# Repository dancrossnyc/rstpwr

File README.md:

# rstpwr

This is, fundamentally, a set of serial-controlled solid-state
switches.  I used them to control the power and reset functions
of development machines with ATX motherboards.

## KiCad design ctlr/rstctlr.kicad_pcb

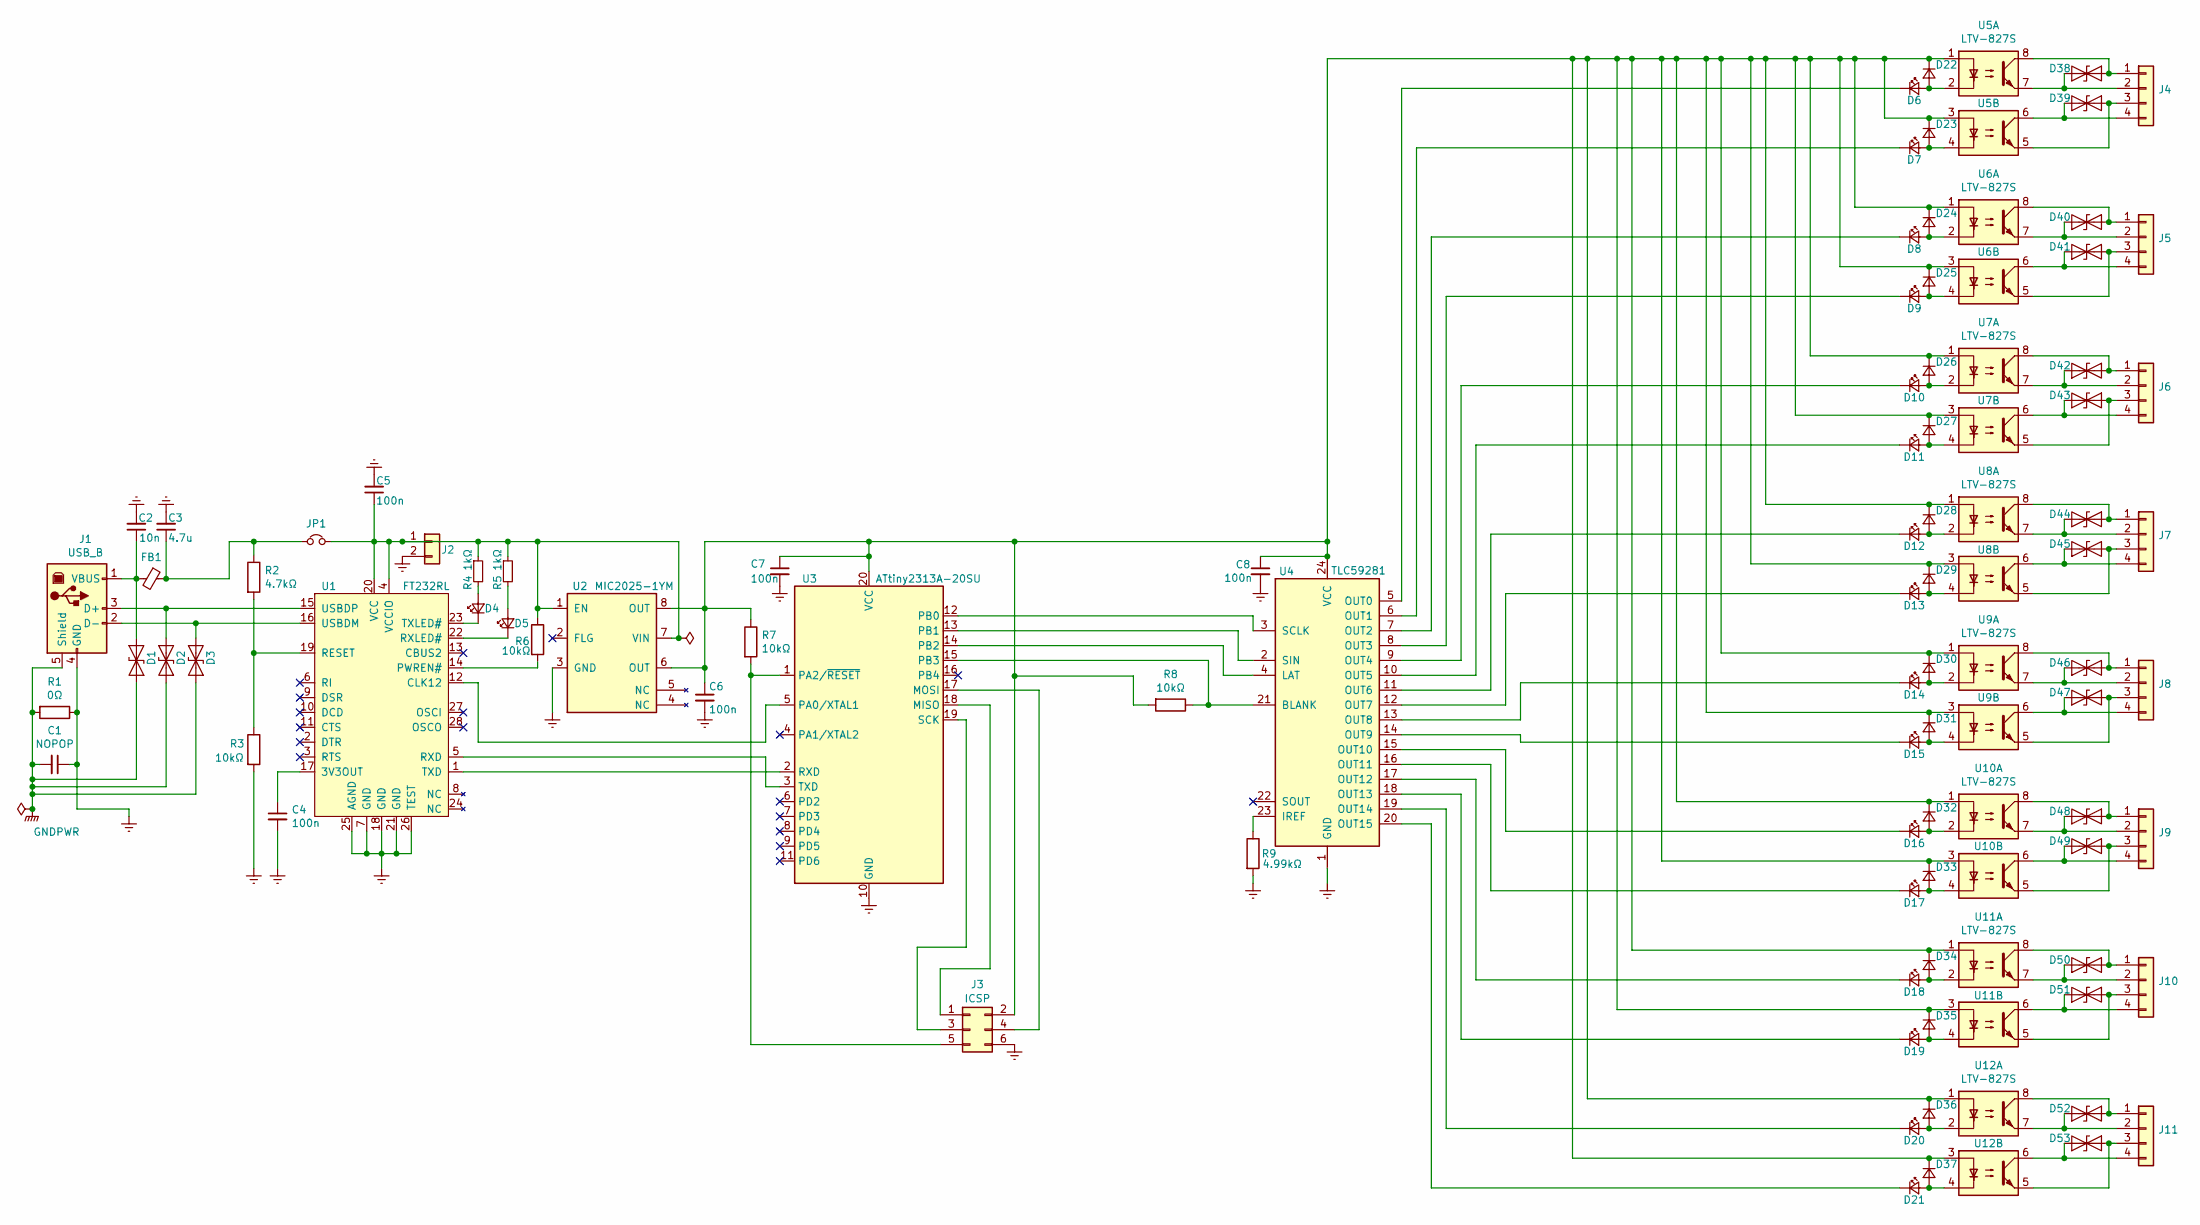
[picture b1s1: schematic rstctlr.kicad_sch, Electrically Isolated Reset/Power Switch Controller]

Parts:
C1: NOPOP; C_0805_2012Metric
C2: 10n; C_0805_2012Metric
C3: 4.7u; C_0805_2012Metric
C4, C5, C6, C7, C8: 100n; C_0805_2012Metric
D1, D2, D3, D22, D23, D24, D25, D26, D27, D28, D29, D30, D31, D32, D33, D34, D35, D36, D37: D_0805_2012Metric
D4, D6, D8, D10, D12, D14, D16, D18, D20: RED; LED_0805_2012Metric
D5, D7, D9, D11, D13, D15, D17, D19, D21: GRN; LED_0805_2012Metric
D38, D39, D40, D41, D42, D43, D44, D45, D46, D47, D48, D49, D50, D51, D52, D53: D_SOD-323_HandSoldering
FB1: FB; L_0805_2012Metric
J1: USB_B; USB_B_OST_USB-B1HSxx_Horizontal
J2: PinHeader_1x02_P2.54mm_Vertical
J3: ICSP; PinHeader_2x03_P2.54mm_Vertical
J4, J5, J6, J7, J8, J9, J10, J11: Molex_SPOX_5267-04A_1x04_P2.50mm_Vertical
JP1: PinHeader_1x02_P2.54mm_Vertical
R1: 0Ω; R_0805_2012Metric
R2: 4.7kΩ; R_0805_2012Metric
R3, R6, R7, R8: 10kΩ; R_0805_2012Metric
R4, R5: 1kΩ; R_0805_2012Metric
R9: 4.99kΩ; R_0805_2012Metric
U1: FT232RL; SSOP-28_5.3x10.2mm_P0.65mm
U2: MIC2025-1YM; SOIC-8_3.9x4.9mm_P1.27mm
U3: ATtiny2313A-20SU; SOIC-20W_7.5x12.8mm_P1.27mm
U4: TLC59281; SSOP-24_3.9x8.7mm_P0.635mm
U5, U6, U7, U8, U9, U10, U11, U12: LTV-827S; SMDIP-8_W9.53mm

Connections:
Earth: C1.1, C2.2, C3.2, C4.2, C5.2, C6.2, C7.2, C8.2, J1.4 (GND), J2.2, J3.6, R1.1, R3.2, R9.2, U1.7 (GND), U1.18 (GND), U1.21 (GND), U1.25 (AGND), U1.26 (TEST), U2.3 (GND), U3.10 (GND), U4.1 (GND)
GNDPWR: C1.2, D1.2 (A2), D2.2 (A2), D3.2 (A2), J1.5 (Shield), R1.2
unnamed: C2.1, D1.1 (A1), FB1.2, J1.1 (VBUS)
unnamed: C3.1, FB1.1, JP1.1, R2.1
unnamed: C4.1, U1.17 (3V3OUT)
unnamed: C5.1, J2.1, JP1.2, R4.1, R5.1, R6.1, U1.4 (VCCIO), U1.20 (VCC), U2.1 (EN), U2.7 (VIN)
unnamed: C6.1, C7.1, C8.1, D22.1 (K), D23.1 (K), D24.1 (K), D25.1 (K), D26.1 (K), D27.1 (K), D28.1 (K), D29.1 (K), D30.1 (K), D31.1 (K), D32.1 (K), D33.1 (K), D34.1 (K), D35.1 (K), D36.1 (K), D37.1 (K), J3.2, R7.1, R8.2, U2.6 (OUT), U2.8 (OUT), U3.20 (VCC), U4.24 (VCC), U5.1, U5.3, U6.1, U6.3, U7.1, U7.3, U8.1, U8.3, U9.1, U9.3, U10.1, U10.3, U11.1, U11.3, U12.1, U12.3
unnamed: D2.1 (A1), J1.3 (D+), U1.15 (USBDP)
unnamed: D3.1 (A1), J1.2 (D-), U1.16 (USBDM)
unnamed: D4.1 (K), U1.23 (TXLED#)
unnamed: D4.2 (A), R4.2
unnamed: D5.1 (K), U1.22 (RXLED#)
unnamed: D5.2 (A), R5.2
unnamed: D6.1 (K), U4.5 (OUT0)
unnamed: D7.1 (K), U4.6 (OUT1)
unnamed: D8.1 (K), U4.7 (OUT2)
unnamed: D9.1 (K), U4.8 (OUT3)
unnamed: D10.1 (K), U4.9 (OUT4)
unnamed: D10.2 (A), D26.2 (A), U7.2
unnamed: D11.1 (K), U4.10 (OUT5)
unnamed: D11.2 (A), D27.2 (A), U7.4
unnamed: D12.1 (K), U4.11 (OUT6)
unnamed: D12.2 (A), D28.2 (A), U8.2
unnamed: D13.1 (K), U4.12 (OUT7)
unnamed: D13.2 (A), D29.2 (A), U8.4
unnamed: D14.1 (K), U4.13 (OUT8)
unnamed: D14.2 (A), D30.2 (A), U9.2
unnamed: D15.1 (K), U4.14 (OUT9)
unnamed: D15.2 (A), D31.2 (A), U9.4
unnamed: D16.1 (K), U4.15 (OUT10)
unnamed: D16.2 (A), D32.2 (A), U10.2
unnamed: D17.1 (K), U4.16 (OUT11)
unnamed: D17.2 (A), D33.2 (A), U10.4
unnamed: D18.1 (K), U4.17 (OUT12)
unnamed: D18.2 (A), D34.2 (A), U11.2
unnamed: D19.1 (K), U4.18 (OUT13)
unnamed: D19.2 (A), D35.2 (A), U11.4
unnamed: D20.1 (K), U4.19 (OUT14)
unnamed: D20.2 (A), D36.2 (A), U12.2
unnamed: D21.1 (K), U4.20 (OUT15)
unnamed: D21.2 (A), D37.2 (A), U12.4
unnamed: D6.2 (A), D22.2 (A), U5.2
unnamed: D7.2 (A), D23.2 (A), U5.4
unnamed: D8.2 (A), D24.2 (A), U6.2
unnamed: D9.2 (A), D25.2 (A), U6.4
unnamed: D38.1 (A1), J4.1, U5.8
unnamed: D38.2 (A2), J4.2, U5.7
unnamed: D39.1 (A1), J4.3, U5.5
unnamed: D39.2 (A2), J4.4, U5.6
unnamed: D40.1 (A1), J5.1, U6.8
unnamed: D40.2 (A2), J5.2, U6.7
unnamed: D41.1 (A1), J5.3, U6.5
unnamed: D41.2 (A2), J5.4, U6.6
unnamed: D42.1 (A1), J6.1, U7.8
unnamed: D42.2 (A2), J6.2, U7.7
unnamed: D43.1 (A1), J6.3, U7.5
unnamed: D43.2 (A2), J6.4, U7.6
unnamed: D44.1 (A1), J7.1, U8.8
unnamed: D44.2 (A2), J7.2, U8.7
unnamed: D45.1 (A1), J7.3, U8.5
unnamed: D45.2 (A2), J7.4, U8.6
unnamed: D46.1 (A1), J8.1, U9.8
unnamed: D46.2 (A2), J8.2, U9.7
unnamed: D47.1 (A1), J8.3, U9.5
unnamed: D47.2 (A2), J8.4, U9.6
unnamed: D48.1 (A1), J9.1, U10.8
unnamed: D48.2 (A2), J9.2, U10.7
unnamed: D49.1 (A1), J9.3, U10.5
unnamed: D49.2 (A2), J9.4, U10.6
unnamed: D50.1 (A1), J10.1, U11.8
unnamed: D50.2 (A2), J10.2, U11.7
unnamed: D51.1 (A1), J10.3, U11.5
unnamed: D51.2 (A2), J10.4, U11.6
unnamed: D52.1 (A1), J11.1, U12.8
unnamed: D52.2 (A2), J11.2, U12.7
unnamed: D53.1 (A1), J11.3, U12.5
unnamed: D53.2 (A2), J11.4, U12.6
unnamed: J3.1, U3.18 (MISO)
unnamed: J3.3, U3.19 (SCK)
unnamed: J3.4, U3.17 (MOSI)
unnamed: J3.5, R7.2, U3.1 (PA2/~RESET)
unnamed: R2.2, R3.1, U1.19 (RESET)
unnamed: R6.2, U1.14 (PWREN#)
unnamed: R8.1, U3.15 (PB3), U4.21 (BLANK)
unnamed: R9.1, U4.23 (IREF)
unnamed: U1.1 (TXD), U3.2 (RXD)
unnamed: U1.5 (RXD), U3.3 (TXD)
unnamed: U1.12 (CLK12), U3.5 (PA0/XTAL1)
unnamed: U3.12 (PB0), U4.3 (SCLK)
unnamed: U3.13 (PB1), U4.2 (SIN)
unnamed: U3.14 (PB2), U4.4 (LAT)

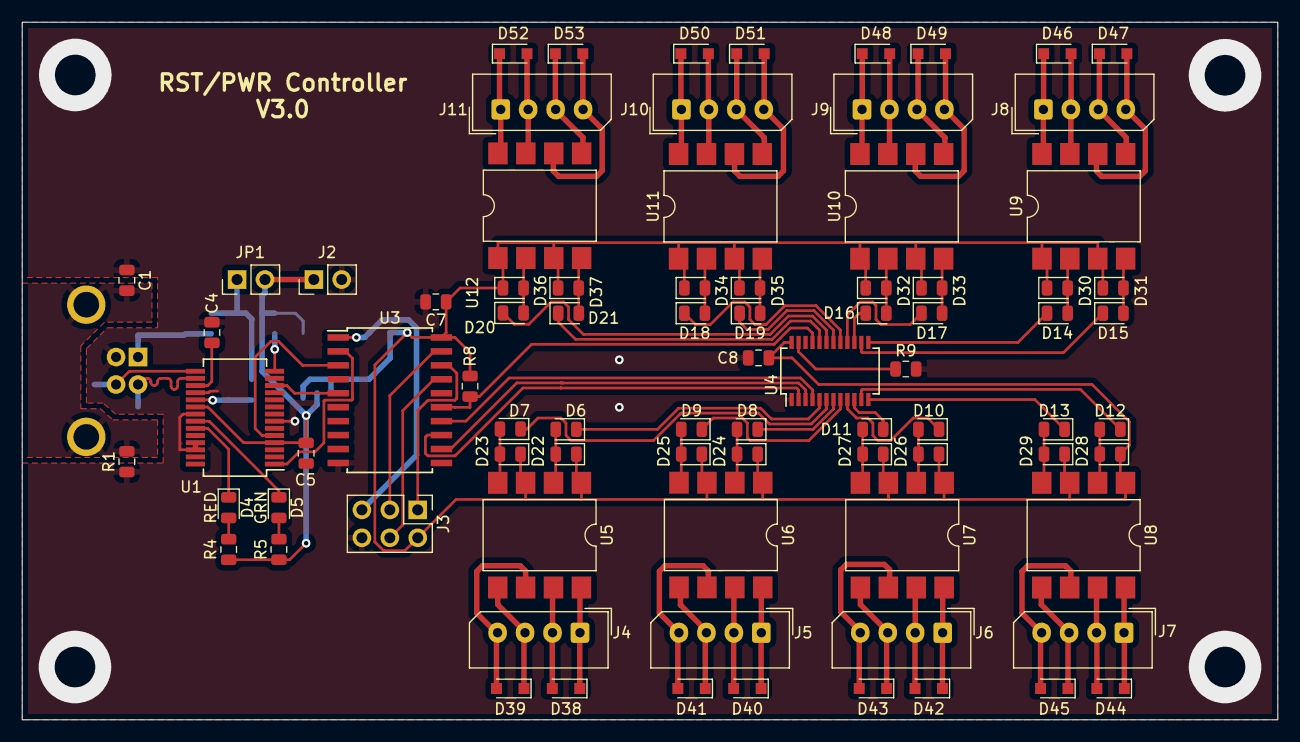
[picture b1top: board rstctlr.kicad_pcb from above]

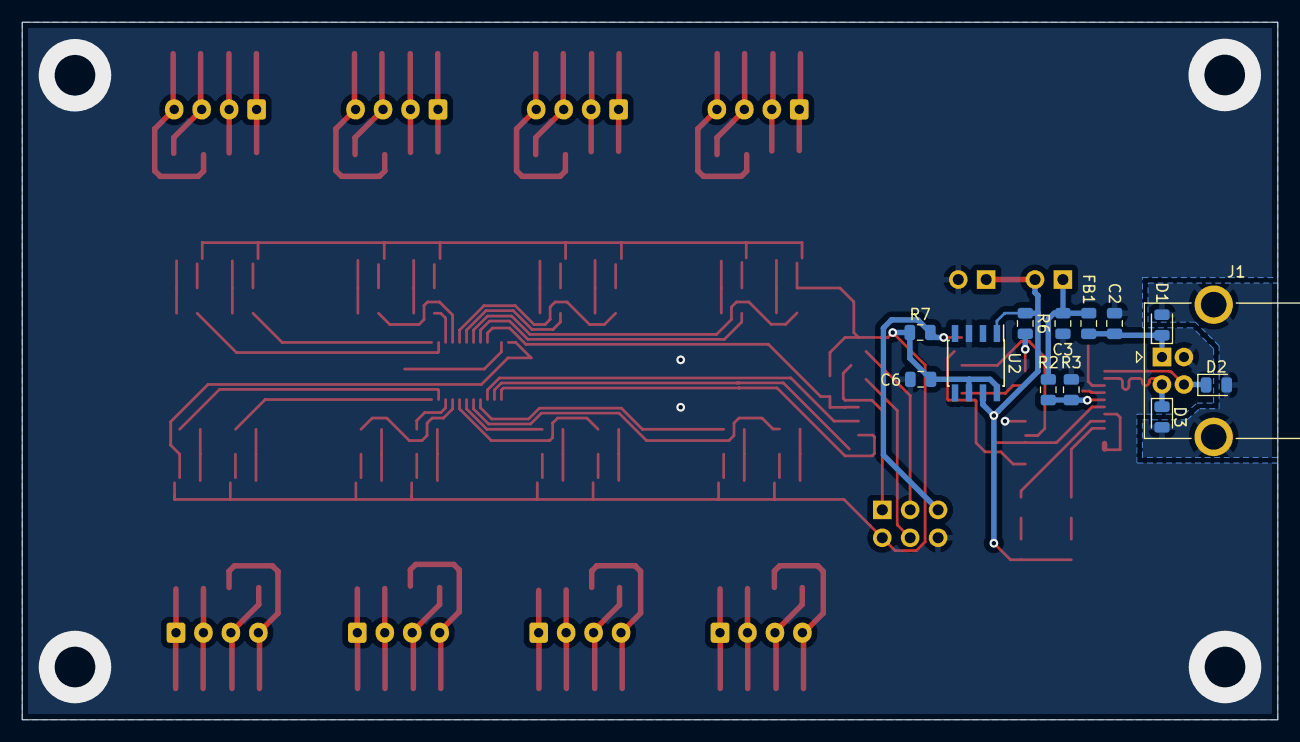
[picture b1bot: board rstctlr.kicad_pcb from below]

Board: 2 copper layers, 114.3 x 63.5 mm, 95 parts (13 on the bottom side), 91 nets.

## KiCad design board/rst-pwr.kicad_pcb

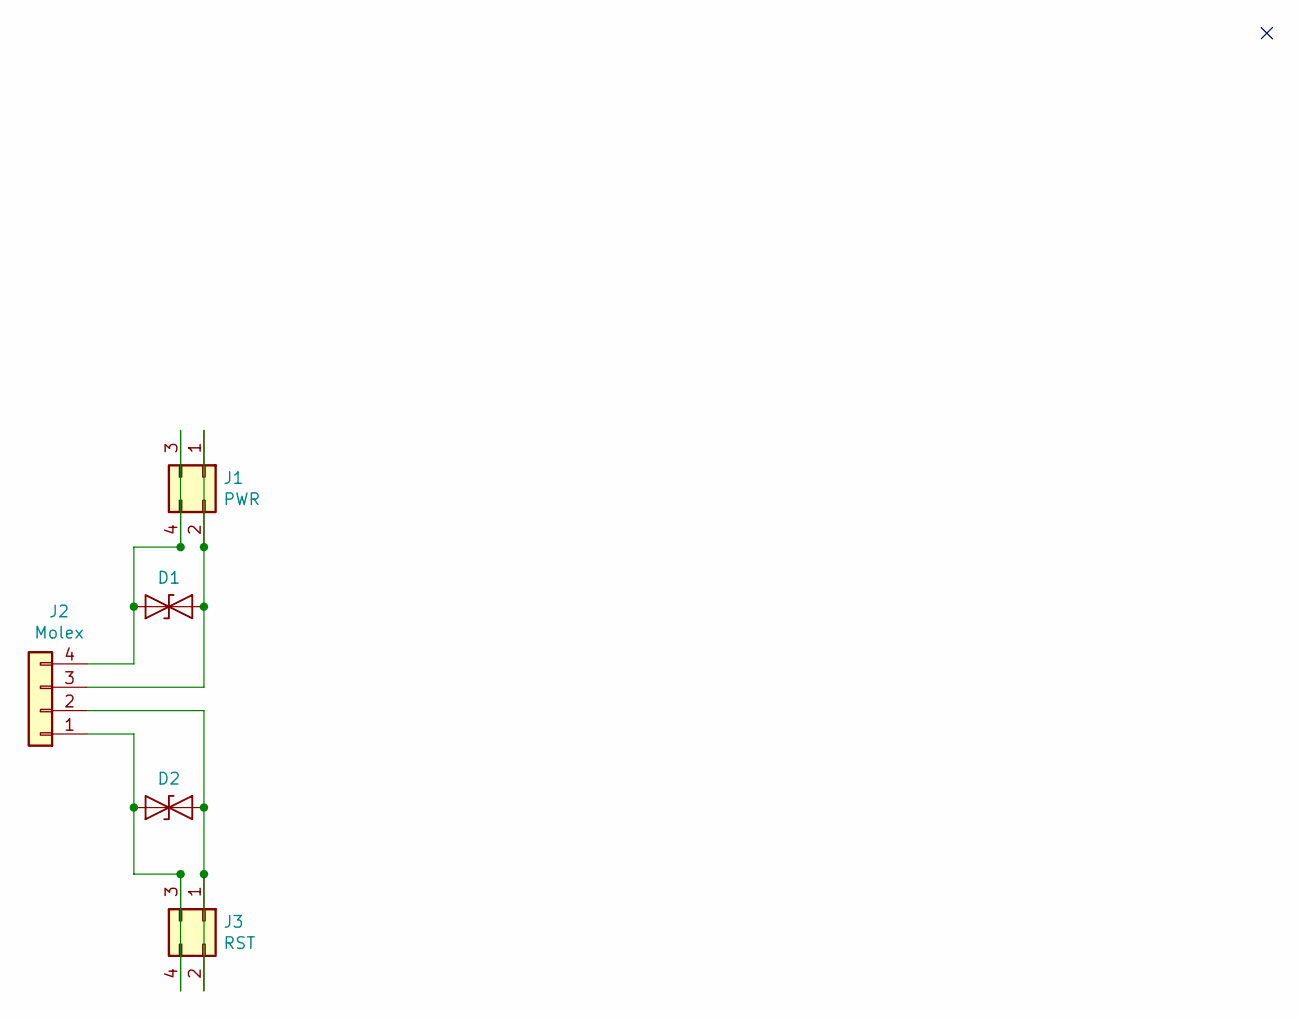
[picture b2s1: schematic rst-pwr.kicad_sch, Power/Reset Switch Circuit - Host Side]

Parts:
D1, D2: D_SOD-323_HandSoldering
J1: PWR; PinHeader_2x02_P2.54mm_Vertical
J2: Molex; Connector
J3: RST; PinHeader_2x02_P2.54mm_Vertical

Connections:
unnamed: D1.1 (A1), J1.1, J1.2, J2.3
unnamed: D1.2 (A2), J1.3, J1.4, J2.4
unnamed: D2.1 (A1), J2.2, J3.1, J3.2
unnamed: D2.2 (A2), J2.1, J3.3, J3.4

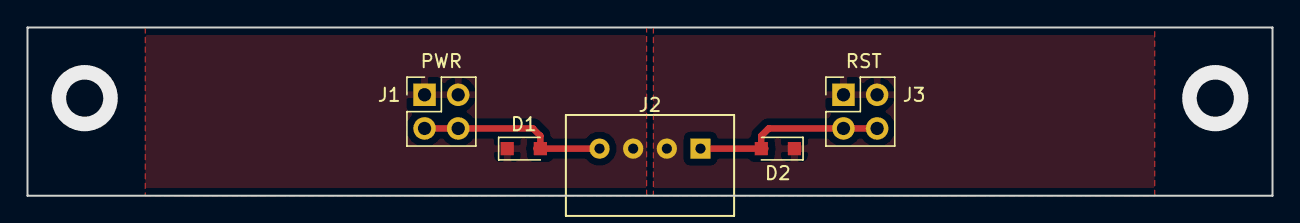
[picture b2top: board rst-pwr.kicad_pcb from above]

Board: 2 copper layers, 94.0 x 12.7 mm, 5 parts (0 on the bottom side), 4 nets.

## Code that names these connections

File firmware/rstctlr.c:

// Reset/Power switch controller.

#include <avr/interrupt.h>
#include <avr/io.h>
#include <string.h>
#include <util/delay.h>

typedef unsigned char byte;
typedef unsigned int size_t;

uint16_t pinstate = 0;

const char DIGITS[] = "0123456789ABCDEF";
const char digits[] = "0123456789acdefg";

enum {
	SCLK  = 0,	// TLC59281 shift clock is PB0.
	SIN = 1,	// ...serial in is PB1.
	LAT = 2,	// ...latch is PB2.
	BLANK = 3,	// ...blank is PB3 (pulled high).
};

inline static void
delayn(int n)
{
	for (int k = 0; k < n; ++k)
		_delay_us(1);
}

inline static void
delay()
{
	delayn(1);
}

void
setoutput(int pin)
{
	DDRB |= (1<<pin);
}

void
pinhi(int pin)
{
	PORTB |= (1<<pin);
}

void
pinlo(int pin)
{
	PORTB &= ~(1<<pin);
}

void
sclock()
{
	pinhi(SCLK);
	delay();
	pinlo(SCLK);
}

void
shift(int bit)
{
	if (bit != 0) {
		pinhi(SIN);
		delay();
	}
	sclock();
	delay();
	pinlo(SIN);
	delay();
}

void
latch()
{
	pinhi(LAT);
	delay();
	pinlo(LAT);
	delay();
}

void
emitstate(uint16_t pinstate)
{
	for (int k = 0; k < 16; ++k)
		shift((pinstate >> k) & 1);
	latch();
}

void
blank()
{
	pinstate = 0U;
	pinhi(BLANK);
	delayn(10);
	emitstate(pinstate);
	pinlo(BLANK);
	delayn(10);
}

void
inituart()
{
	const unsigned long BAUD_RATE = 9600UL;

	const unsigned long prescale = ((F_CPU / 16UL + BAUD_RATE / 2) / BAUD_RATE) - 1UL;
	UBRRH = prescale >> 8;
	UBRRL = prescale;
	UCSRB = /*(1 << RXCIE) |*/ (1 << RXEN) | (1 << TXEN);
	UCSRC = (1 << UCSZ0) | (1 << UCSZ1);
}

void
initmcu()
{
	setoutput(SCLK);
	setoutput(SIN);
	setoutput(LAT);
	setoutput(BLANK);

	blank();
	inituart();
}

enum CMDState {
	CmdREADING,
	CmdERROR,
};

enum {
	RbOK = 0,
	RbOVERFLOW = 1,
	RbUNDERFLOW = 2,

	CAPACITY = 16,
};

typedef struct RingBuffer RingBuffer;
struct RingBuffer {
	volatile byte buffer[CAPACITY];
	volatile size_t readidx, writeidx;
};

inline size_t
rblen(volatile RingBuffer *buffer)
{
	return buffer->writeidx - buffer->readidx;
}

inline int
rbempty(volatile RingBuffer *buffer)
{
	return rblen(buffer) == 0;
}

inline int
rbfull(volatile RingBuffer *buffer)
{
	return rblen(buffer) == CAPACITY;
}

int
rbinsert(volatile RingBuffer *buffer, byte b)
{
	if (rbfull(buffer))
		return RbOVERFLOW;
	buffer->buffer[buffer->writeidx % CAPACITY] = b;
	buffer->writeidx++;
	return RbOK;
}

int
rbremove(volatile RingBuffer *buffer, byte *b)
{
	if (rbempty(buffer))
		return RbUNDERFLOW;
	*b = buffer->buffer[buffer->readidx % CAPACITY];
	buffer->readidx++;
	return RbOK;
}

volatile enum CMDState cmdstate = CmdREADING;
volatile RingBuffer readbuf = { { 0 }, 0, 0 };

byte
uartgetc()
{
	while ((UCSRA & (1 << RXC)) == 0)
		;
	byte b = UDR;
	return b;
}

void
fakeisr()
{
	int b = uartgetc();
	if (cmdstate == CmdERROR) {
		if (b == '\n')
			cmdstate = CmdREADING;
		return;
	}
	if (rbinsert(&readbuf, b) != RbOK)
		cmdstate = CmdERROR;
}

int
fakereadc()
{
	byte b;

	fakeisr();
	while (rbremove(&readbuf, &b) != RbOK)
		fakeisr();

	return b;
}

#define readc fakereadc


/*
ISR(USART_RX_vect, ISR_BLOCK) {
	int b = uartgetc();
	if (cmdstate == CmdERROR) {
		if (b == '\n')
			cmdstate = CmdREADING;
		return;
	}
	if (rbinsert(&readbuf, b) != RbOK)
		cmdstate = CmdERROR;
}

void
wfi()
{
	asm volatile("sei;sleep;cli" :::);
}

void
nop()
{
	asm volatile("nop" :::);
}

void
probeintr()
{
	sei();
	nop();
	cli();
}

int
readc()
{
	byte b;

	probeintr();
	while (rbremove(&readbuf, &b) != RbOK)
		wfi();

	return b;
}
*/

size_t
readcmd(char *buffer, size_t size)
{
	size_t k = 0;
	while (k < size) {
		int b = readc();
		if (b == '\r')
			continue;
		buffer[k++] = b;
		if (b == '\n') {
			return k;
		}
	}
	cmdstate = CmdERROR;
	return ~0;
}

void
uartputc(byte b)
{
	while ((UCSRA & (1 << UDRE)) == 0)
		;
	UDR = b;
	while ((UCSRA & (1 << TXC)) == 0)
		;
}

void
reply(const char __flash *s)
{
	for (const char __flash *p = s; *p != '\0'; ++p)
		uartputc(*p);
}


int
hexdigit(char digit)
{
	for (const char *p = DIGITS; *p != '\0'; ++p)
		if (*p == digit)
			return(p - DIGITS);
	for (const char *p = digits; *p != '\0'; ++p)
		if (*p == digit)
			return(p - digits);

	return -1;
}

int
hexbyte(const char hex[2])
{
	int digit0, digit1;

	digit0 = hexdigit(hex[0]);
	if (digit0 < 0)
		return -1;
	digit1 = hexdigit(hex[1]);
	if (digit1 < 0)
		return -1;

	return (digit0 << 4) + digit1;
}

const char __flash EBADMSG[] = "!msg\r\n";
const char __flash EBADCMD[] = "!cmd\r\n";
const char __flash EBADPORT[] = "!port\r\n";
const char __flash EBADCKSUM[] = "!cksum\r\n";

const char __flash OK[] = "+ok\r\n";

void
evalreset(const char *cmd, size_t len)
{
	if (len != 7 || cmd[6] != '\n') {
		reply(EBADMSG);
		return;
	}
	if (memcmp(cmd, "RST#", 4) != 0) {
		reply(EBADCMD);
		return;
	}
	if (memcmp(cmd + 4, "E4", 2) != 0) {
		reply(EBADCKSUM);
		return;
	}
	blank();
	reply(OK);
}

// Commands are simple strings of the form:
// IPP#CS\n
void
evalcmd(const char *cmd, size_t len)
{
	if (len != 7 || cmd[6] != '\n') {
		reply(EBADMSG);
		return;
	}

	if (cmd[0] == 'R') {
		evalreset(cmd, len);
		return;
	}

	if (cmd[0] != 'I' && cmd[0] != 'O') {
		reply(EBADCMD);
		return;
	}

	int hex = hexbyte(cmd + 1);
	if (hex < 0 || hex >= 16) {
		reply(EBADPORT);
		return;
	}
	int port = hex;

	if (cmd[3] != '#') {
		reply(EBADMSG);
		return;
	}
	hex = hexbyte(cmd + 4);
	if (hex < 0) {
		reply(EBADMSG);
		return;
	}
	unsigned int cksum = hex;
	for (int k = 0; k < 4; ++k)
		cksum += cmd[k];
	cksum &= 0xFF;
	if (cksum != 0) {
		reply(EBADCKSUM);
		return;
	}

	if (cmd[0] == 'I')
		pinstate |= (1U << port);
	else
		pinstate &= ~(1U << port);
	emitstate(pinstate);

	reply(OK);
}

int
main()
{
	initmcu();

	for (;;) {
		char cmd[8];
		size_t len = readcmd(cmd, sizeof(cmd));
		if (len >= sizeof(cmd))
			continue;
		cmd[len] = '\0';
		evalcmd(cmd, len);
	}

	return 0;
}

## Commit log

2021-03-25 Initial revision.
2021-05-04 Update to KiCad6.
2021-11-18 Updates for new KiCad version.
2021-11-18 rstctlr: adjust USB trace length, fix stylesheets
2021-11-18 rstctlr: bump version number.
2021-11-18 rstctlr: Gerber output directory updates
2025-07-15 update: internal KiCad formatting etc changes
